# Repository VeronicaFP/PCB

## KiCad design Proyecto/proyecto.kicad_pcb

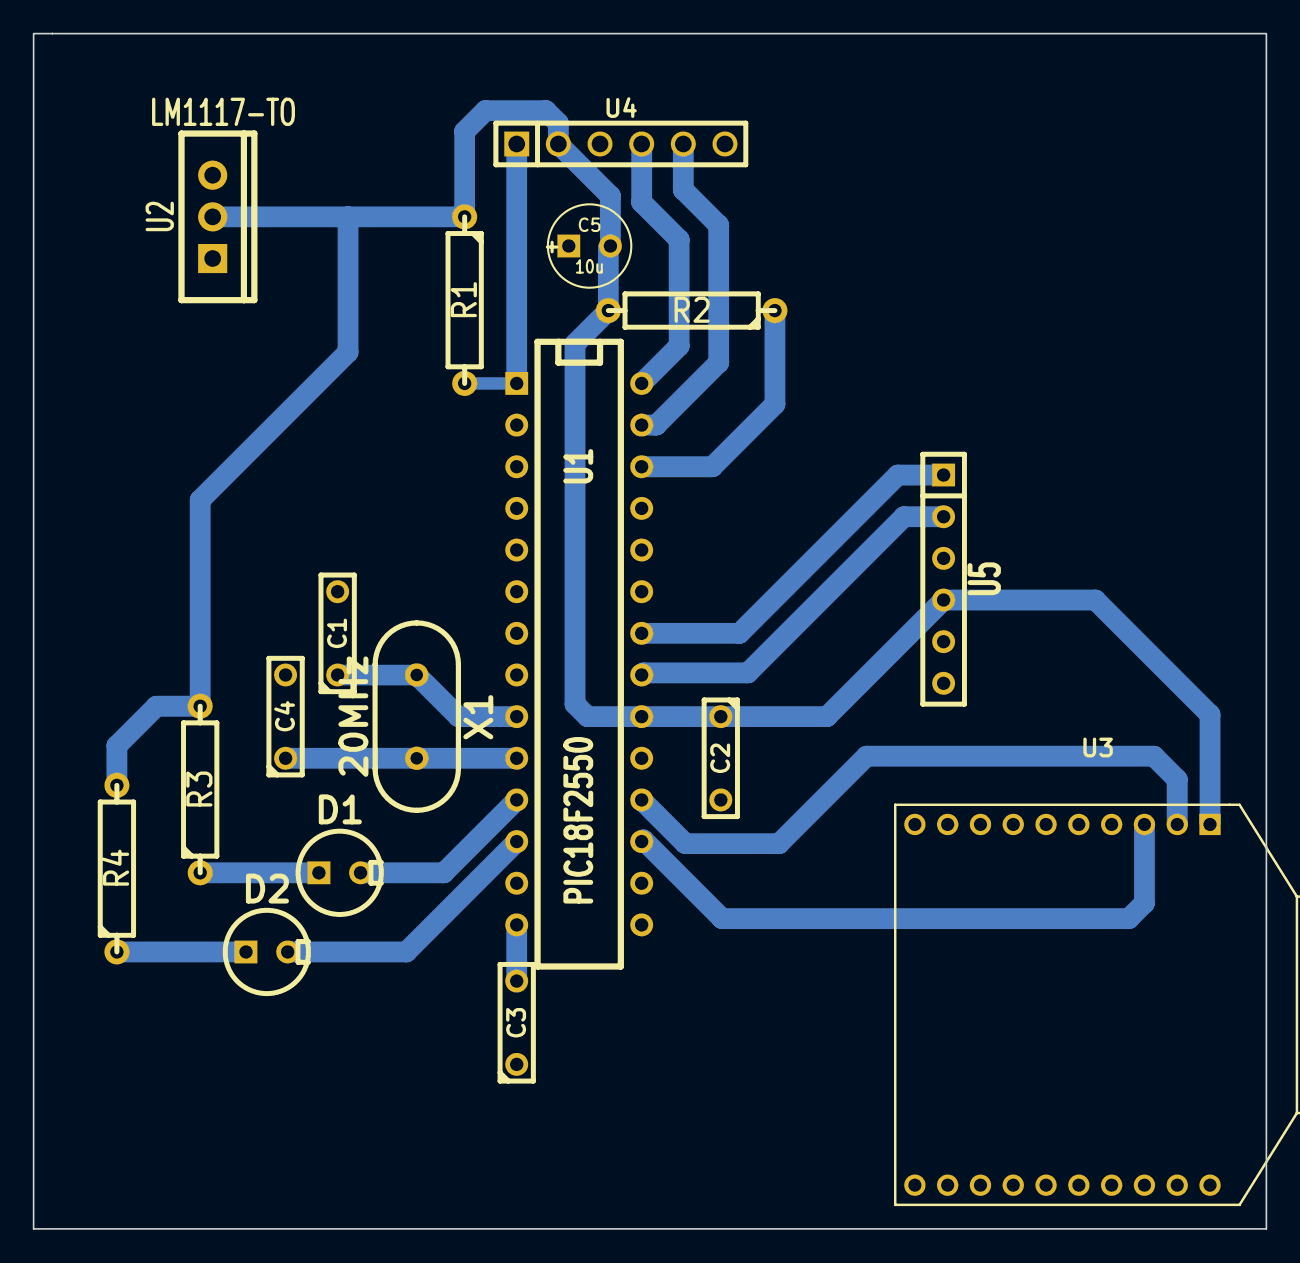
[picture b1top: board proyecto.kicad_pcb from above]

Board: 2 copper layers, 75.2 x 72.9 mm, 17 parts (0 on the bottom side), 17 nets.

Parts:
C1, C4: 22p; C2
C2: 100n; C2
C3: 470n; C2
C5: 10u; C1V5
D1, D2: LED; LEDV
R1, R2: 10k; R4
R3, R4: 330; R4
U1: PIC18F2550; DIP-28__300
U2: LM1117-TO; TO220_VERT_a
U3: RN42XV
U4: PICKIT3; PIN_ARRAY-6X1
U5: POLOLUV1; SIL-6
X1: 20MHz; HC-49V

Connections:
/3V3: C2.1, C5.2, R1.1, R2.2, R3.2, R4.2, U1.20, U2.2, U3.1, U4.2, U5.4
/MCLR: R1.2, U1.1, U4.1
/PGC: U1.27, U4.5
/PGD: U1.28, U4.4
/RX: U1.18, U3.2
/SCL: U1.22, U5.1
/SDA: U1.21, U5.2
/TX: U1.17, U3.3
GND: C1.2, C2.2, C3.1, C4.2, C5.1, U1.8, U1.19, U2.3, U3.10, U3.16, U4.3, U5.3
unnamed: C3.2, U1.14
unnamed: C1.1, U1.9, X1.1
unnamed: C4.1, U1.10, X1.2
unnamed: R2.1, U1.26
unnamed: D1.2, U1.11
unnamed: D2.2, U1.12
unnamed: D1.1, R3.1
unnamed: D2.1, R4.1

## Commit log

2014-11-19 :lollipop: Added .gitattributes & .gitignore files
2014-11-19 Diseño Placa
2014-11-20 Placa
